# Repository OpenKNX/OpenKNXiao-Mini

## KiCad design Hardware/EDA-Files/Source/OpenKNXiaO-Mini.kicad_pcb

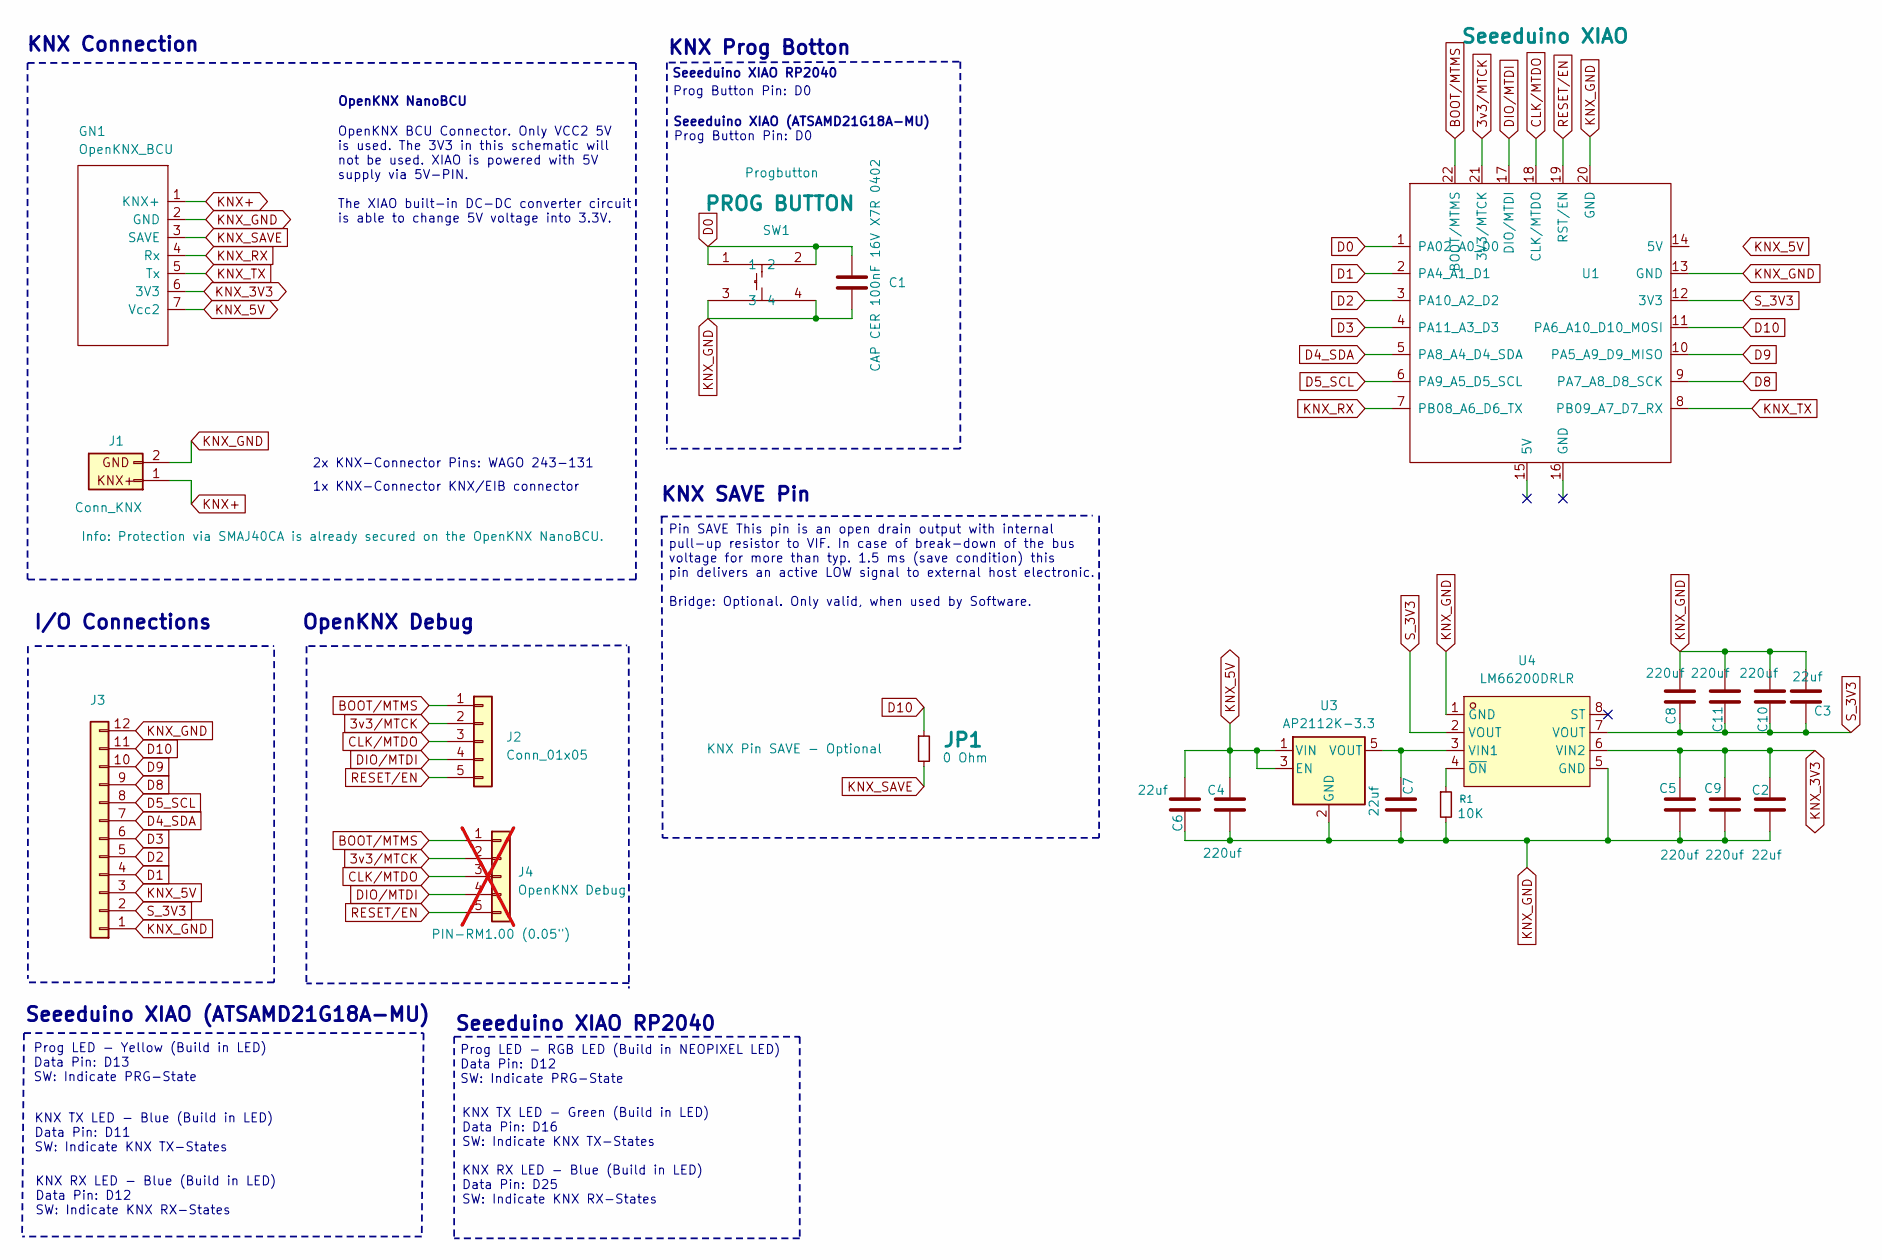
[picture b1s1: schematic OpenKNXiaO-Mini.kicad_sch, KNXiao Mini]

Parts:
C1: CAP CER 100nF 16V X7R 0402; C_0402_1005Metric; lcsc C1525
C2, C3, C6, C7: 22uf; C_0402_1005Metric; LCSC C105226
C4, C5, C8, C9, C10, C11: 220uf; C_1206_3216Metric; LCSC C412252
GN1: OpenKNX_BCU; OpenKNX_BCU_V2.0
J1: Conn_KNX; KNX-Connector-SMD-Flat
J2: Conn_01x05; PinHeader_1x05_P1.00mm_Vertical
J3: JST SHL SM12B SHLS TF 1x12-1MP P1.00mm Horizontal; JST_SHL_SM12B-SHLS-TF_1x12-1MP_P1.00mm_Horizontal; lcsc C160411
J4: OpenKNX Debug; JST_SH_BM05B-SRSS-TB_1x05-1MP_P1.00mm_Vertical; lcsc C160391; not fitted
JP1: 0 Ohm; R_0603_1608Metric_Pad0.98x0.95mm_HandSolder
R1: 10K; R_0402_1005Metric; lcsc C25744
SW1: SKRPACE010; KEY-SMD_4P-L4.2-W3.2-P2.20-LS4.6; LCSC Part C139797
U1: Seeeduino XIAO; Seeeduino XIAO-MOUDLE14P-2.54-21X17.8MM-no-15-16-17-18-19-2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
U3: AP2112K-3.3; SOT-23-5; lcsc C51118
U4: LM66200DRLR; SOT-583-8_L2.1-W1.2-P0.50-LS1.6-BL; LCSC Part C3235556

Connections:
3v3/MTCK: J2.2, U1.21 (3V3/MTCK)
BOOT/MTMS: J2.1, U1.22 (BOOT/MTMS)
CLK/MTDO: J2.3, U1.18 (CLK/MTDO)
D0: C1.1, SW1.1, SW1.2, U1.1 (PA02_A0_D0)
D1: J3.4, U1.2 (PA4_A1_D1)
D2: J3.5, U1.3 (PA10_A2_D2)
D3: J3.6, U1.4 (PA11_A3_D3)
D4_SDA: J3.7, U1.5 (PA8_A4_D4_SDA)
D5_SCL: J3.8, U1.6 (PA9_A5_D5_SCL)
D8: J3.9, U1.9 (PA7_A8_D8_SCK)
D9: J3.10, U1.10 (PA5_A9_D9_MISO)
D10: J3.11, JP1.1, U1.11 (PA6_A10_D10_MOSI)
DIO/MTDI: J2.4, U1.17 (DIO/MTDI)
KNX+: GN1.1 (KNX+), J1.1
KNX_3V3: C2.2, C5.1, C9.1, GN1.6 (3V3), U4.6 (VIN2)
KNX_5V: C4.1, C6.2, GN1.7 (Vcc2), J3.3, U3.1 (VIN), U3.3 (EN)
KNX_GND: C1.2, C2.1, C3.1, C4.2, C5.2, C6.1, C7.2, C8.1, C9.2, C10.2, C11.2, GN1.2 (GND), J1.2, J3.1, J3.12, R1.2, SW1.3, SW1.4, U1.13 (GND), U1.20 (GND), U3.2 (GND), U4.1 (GND), U4.5 (GND)
KNX_RX: GN1.4 (Rx), U1.7 (PB08_A6_D6_TX)
KNX_SAVE: GN1.3 (SAVE), JP1.2
KNX_TX: GN1.5 (Tx), U1.8 (PB09_A7_D7_RX)
unnamed: C7.1, U3.5 (VOUT), U4.3 (VIN1)
unnamed: R1.1, U4.4 (~ON)
RESET/EN: J2.5, U1.19 (RST/EN)
S_3V3: C3.2, C8.2, C10.1, C11.1, J3.2, U1.12 (3V3), U4.2 (VOUT), U4.7 (VOUT)

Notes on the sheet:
Prog Button Pin: D0
2x KNX-Connector Pins: WAGO 243-131
KNX TX LED - Blue (Build in LED) Data Pin: D11 SW: Indicate KNX TX-States
OpenKNX Debug
Seeeduino XIAO RP2040
OpenKNX BCU Connector. Only VCC2 5V is used. The 3V3 in this schematic will not be used. XIAO is powered with 5V supply via 5V-PIN. The XIAO built-in DC-DC converter circuit is able to change 5V voltage into 3.3V.
Seeeduino XIAO RP2040
Prog LED - RGB LED (Build in NEOPIXEL LED) Data Pin: D12 SW: Indicate PRG-State
Pin SAVE This pin is an open drain output with internal pull-up resistor to VIF. In case of break-down of the bus voltage for more than typ. 1.5 ms (save condition) this pin delivers an active LOW signal to external host electronic. Bridge: Optional. Only valid, when used by Software.
KNX Connection
Seeeduino XIAO (ATSAMD21G18A-MU)
KNX TX LED - Green (Build in LED) Data Pin: D16 SW: Indicate KNX TX-States
OpenKNX NanoBCU
1x KNX-Connector KNX/EIB connector
I/O Connections
KNX RX LED - Blue (Build in LED) Data Pin: D25 SW: Indicate KNX RX-States
KNX RX LED - Blue (Build in LED) Data Pin: D12 SW: Indicate KNX RX-States
KNX SAVE Pin
KNX Prog Botton
Prog LED - Yellow (Build in LED) Data Pin: D13 SW: Indicate PRG-State

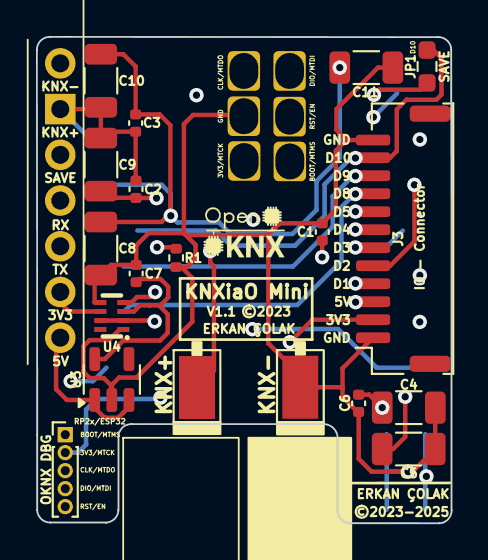
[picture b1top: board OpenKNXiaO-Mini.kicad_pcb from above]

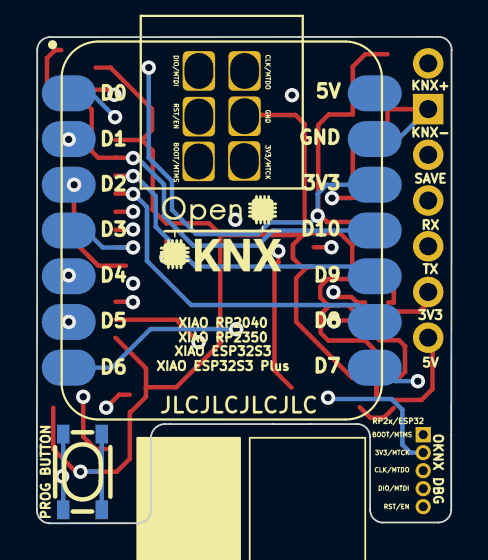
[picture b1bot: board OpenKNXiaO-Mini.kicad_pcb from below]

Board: 4 copper layers, 23.0 x 27.0 mm, 23 parts (3 on the bottom side), 24 nets.

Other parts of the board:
REF1: LOGO; OpenKNX_Logo_05x03
REF2: LOGO; OpenKNX_Logo_07x05

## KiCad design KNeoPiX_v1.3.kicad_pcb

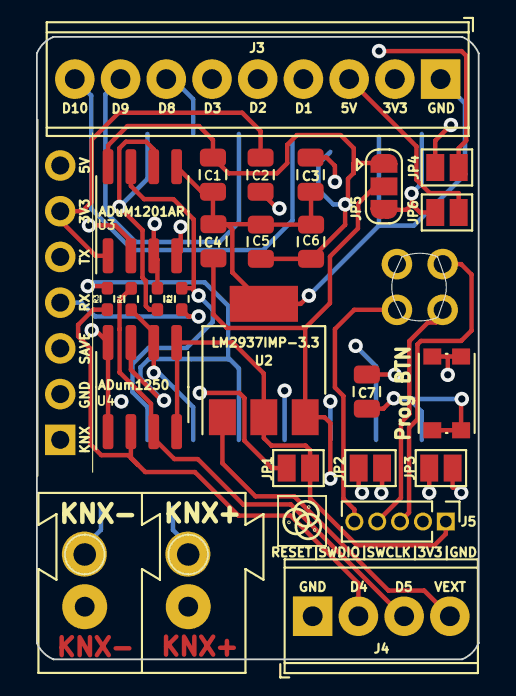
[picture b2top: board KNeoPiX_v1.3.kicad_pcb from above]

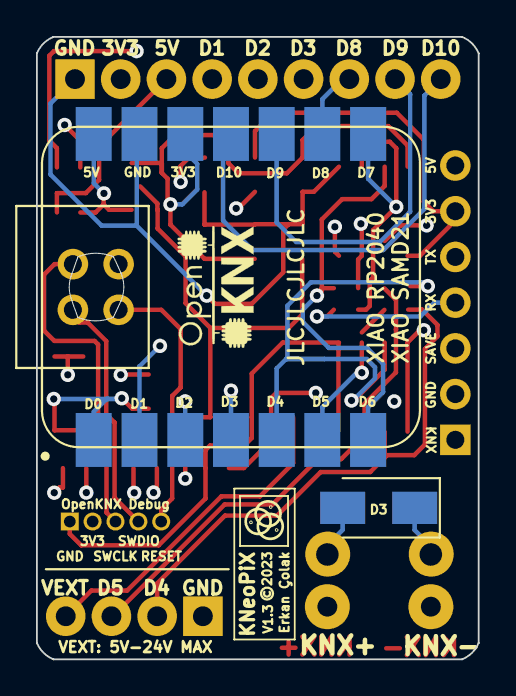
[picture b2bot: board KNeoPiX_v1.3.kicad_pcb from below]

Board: 4 copper layers, 24.5 x 34.6 mm, 31 parts (2 on the bottom side), 28 nets.

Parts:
C1, C2, C5, C6: 100nF; C_0805_2012Metric
C3: 100 nf 25V; C_0805_2012Metric
C4: 10µf 16V; C_0805_2012Metric
C7: 100nF 16V - (X5R 0805); C_0805_2012Metric
D3: SMAJ40CA-13-F; D_SMA
GN1: OpenKNX_BCU; NanoBCU_PinSocket_LowProfile
H1, H2: 243-131; 243131
J1: Conn_KNX; KNX_Connector
J2: Conn_KNX; KNX_Connector_Light
J3: Screw Terminal - Non Isolated IOs; TerminalBlock_Phoenix_MPT-0,5-9-2.54_1x09_P2.54mm_Horizontal
J4: Screw Terminal - Isolated IOs; TerminalBlock_Phoenix_MPT-0,5-4-2.54_1x04_P2.54mm_Horizontal
J5: Conn_01x05; PinHeader_1x05_P1.27mm_Vertical
JP1: GND KNX voltage input; SolderJumper-2_P1.3mm_Open_Pad1.0x1.5mm
JP2: 3V3 KNX voltage input; SolderJumper-2_P1.3mm_Open_Pad1.0x1.5mm
JP3: VCC Direct In/Out 3V3/5V; SolderJumper-2_P1.3mm_Open_Pad1.0x1.5mm
JP4: KNX Pin SAVE - Optional; SolderJumper-2_P1.3mm_Open_Pad1.0x1.5mm
JP5: Select U2 and Input Voltage; SolderJumper-3_P1.3mm_Open_RoundedPad1.0x1.5mm
JP6: 5V KNX voltage input; SolderJumper-2_P1.3mm_Open_Pad1.0x1.5mm
R1: 0Ohm - TXRX Jumper; R_0402_1005Metric_Pad0.72x0.64mm_HandSolder
R2: 0Ohm - RXTX Jumper; R_0402_1005Metric_Pad0.72x0.64mm_HandSolder
R3: 0Ohm - D4 Jumper; R_0402_1005Metric_Pad0.72x0.64mm_HandSolder
R4: 0Ohm - D5 Jumper; R_0402_1005Metric_Pad0.72x0.64mm_HandSolder
SW1: Prog BTN; SW_Push_1P1T_NO_CK_KMR2
U1: Seeeduino XIAO; Seeeduino XIAO-MOUDLE14P-2.54-21X17.8MM-no-15-16-17-18-19-2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
U2: LM2937IMP-3.3 / 5.0; SOT-223-3_TabPin2
U3: ADuM1201AR / ADum1250; SOIC-8_3.9x4.9mm_P1.27mm
U4: ADum1250; SOIC-8_3.9x4.9mm_P1.27mm

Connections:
5V-MCU: JP5.3 (B), JP6.1 (A), U1.14 (5V)
D0: C7.1, SW1.2, U1.1 (PA02_A0_D0)
D1: J3.4, U1.2 (PA4_A1_D1)
D2: J3.5, U1.3 (PA10_A2_D2)
D3: J3.6, U1.4 (PA11_A3_D3)
D4_SDA: R3.2, U1.5 (PA8_A4_D4_SDA), U4.7 (VIA)
D5_SCL: R4.2, U1.6 (PA9_A5_D5_SCL), U4.6 (VOB)
D6_TX: R2.2, U1.7 (PB08_A6_D6_TX), U3.7 (VIA)
D7_RX: R1.2, U1.8 (PB09_A7_D7_RX), U3.6 (VOB)
D8: J3.7, U1.9 (PA7_A8_D8_SCK)
D9: J3.8, U1.10 (PA5_A9_D9_MISO)
D10: J3.9, JP4.2 (B), U1.11 (PA6_A10_D10_MOSI)
EXT_GND: C1.2, C3.2, C4.2, C5.2, C6.1, C7.2, J3.1, J4.1, J5.1, JP1.1 (A), SW1.1, U1.13 (GND), U1.20 (GND), U2.2 (GND), U3.5 (GND2), U4.4 (GND1), U4.5 (GND2)
EXT_VCC_IN: C3.1, J4.4, JP3.1 (A), U2.1 (VI)
EXT_VCC_OUT: C4.1, JP3.2 (B), JP5.2 (C), U2.3 (VO)
KNX+: D3.A, GN1.1 (KNX+), H2.1, J1.1, J2.1
KNX_3V3: C2.1, GN1.6 (3V3), JP2.2 (B), U3.1 (VDD1)
KNX_5V: GN1.7 (Vcc2), J3.3, JP6.2 (B)
KNX_GND: C2.2, D3.C, GN1.2 (GND), H1.1, J1.2, J2.2, JP1.2 (B), U3.4 (GND1)
KNX_RX: GN1.4 (Rx), R2.1, U3.2 (VOA)
KNX_SAVE: GN1.3 (SAVE), JP4.1 (A)
KNX_TX: GN1.5 (Tx), R1.1, U3.3 (VIB)
NEO_DATA0_OUT: J4.2, R3.1, U4.2 (VOA)
NEO_DATA1_OUT: J4.3, R4.1, U4.3 (VIB)
RESET: J5.5, U1.19 (RESET)
SWCLK: J5.3, U1.18 (PA30_SWCLK)
SWDIO: J5.4, U1.17 (PA31_SWDIO)
S_3V3: C1.1, C5.1, C6.2, J3.2, J5.2, JP2.1 (A), JP5.1 (A), U1.12 (3V3), U3.8 (VDD2), U4.1 (VDD1), U4.8 (VDD2)

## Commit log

2023-02-14 Initial - Backup Commit
2023-02-17 initial v7 migration
2023-02-18 WIP - After Migration to KiCad 7
    Add. 4 Layer
    Add. DebugInterface
    Add. Solder Cuts for XIAO - Reset, SWDIO, SWCLK
    New order of all footprints and also rerouting then.
2023-02-19 Pre-Ready for 1st Prod. Needs to be checked again.
2023-02-19 Finalized version v1.3!
    Every is now checked and Ready for 1st pcb production!
    Next todo is to clean up the whole project, files, folders, footprint and also the 3d files.
2023-02-19 CleanUP
2023-02-22 add footprint and symbol libraries cleaned up.
2023-02-22 New footprint, folder structure
    More cleaned UP!
2023-02-22 Cleaned up 3D Models and fabrication
2023-02-23 Final changes before first test production order
    - changed smd pads from rect to oval
    - checked the prog and debug interface (rm1.00!)
    - add. initial scheme PageLayout
    - created production files for first test order
    - add. documentation folder with initial informations
    - updated 3D Model
2023-02-25 Changed the pcb cut-out to customized wholes
    Since a clean cutout costs more. Therefore, lets try with this one.
    Btw. This is also the same cut out on PicoKNeoPix.
2023-02-25 Final Production V1.3!
    Not in production - Little tracks and via cleanups!
2023-02-25 Initial commit OpenKNXIaO Mini
    First alpha version
2023-02-28 OpenKNXiaO - Final form and dimensions are now established.
    Initial housing is startet. Dimensions could be changed later
2023-03-03 Centered KNX connection and first routing
    Updated low high profile (Pin-Header / Low BCU)
    Removed SMA Diode. BCU has allready its own.
2023-03-17 Recheck. Add more ToDo!
2023-03-25 Further Project files...
2023-04-14 Prog. Move to outside
2023-04-22 rearranged Logo & Description position
2023-04-25 Pre-Final
    ToDo - Move Save <--> D10 bridge to a reachable place on the pcb
2023-04-26 Final - Ready for Prototype Production.
    Checked all again!
2023-04-27 Fixed Logo & Version rendering and enabled knx bcu description on back site
2023-04-29 Changed Title and Date
2023-04-29 last circuit check
2023-05-07 NanoBCU - NCN51xx ist nach unten gerichtet.
    Neue Version mit nach unten gerichtetem NCN. Die Kondensatoren sowie die Spulen sind in dieser Variante nach oben Gerichtet. Je nach Anwendung können diese dann mit der Slim oder der normalen Variant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
2023-05-08 Final - Prototype Production Order! V1.0
    Clean-UP prepared for JLCPCB production!
2023-09-03 Initial OpenKNX commit
2023-09-03 Housing: Printable 3D STL files
2023-09-06 External Documentation & PageLayout
    - add. Seeed-Studio-XIAO Series SOM Datasheet pdf to external documentation
    - fixed PageLayout "text"
2025-11-19 First Test Produktion - ESP32S3 Support
2025-11-19 Rel.v1.1 - Waiting for Produktion!
2025-11-23 Just wiring cleanups

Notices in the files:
Hardware/EDA-Files/Source/OpenKNXiaO-Mini.kicad_pcb:
©2023-2025
©2023
